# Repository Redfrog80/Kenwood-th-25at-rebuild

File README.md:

# Kenwood-th-25at-rebuild
Created a battery clam shell so I could replace the dead OEM battery of an old Kenwood handheld radio.
If you wish to replicate the battery using my models, all you need is a cheap usb-c 2S lipo charger, an appropriately sized 2S lipo, and a soldering iron.
If I ever return to this project, I will likely add screw holes so the battery can be dismantled, a physical switch to disconnect the battery from the charge controller (for storage), and a meter to display battery voltage.

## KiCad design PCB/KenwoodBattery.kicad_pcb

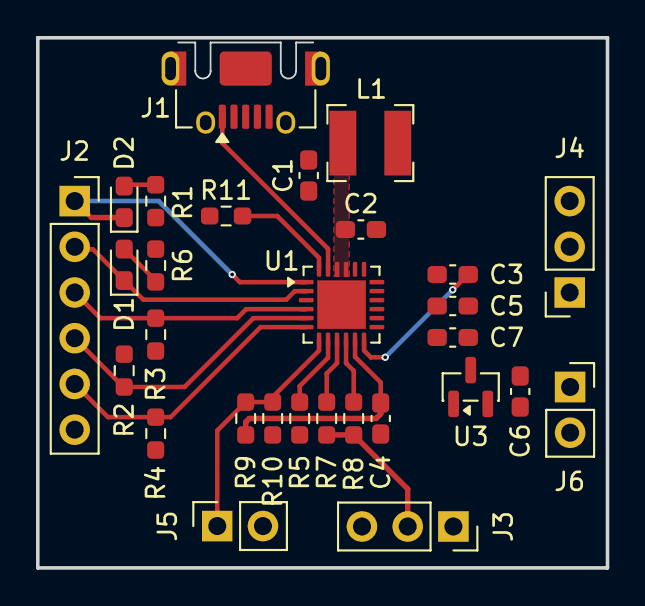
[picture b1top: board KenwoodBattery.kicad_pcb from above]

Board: 2 copper layers, 31.6 x 29.5 mm, 29 parts (0 on the bottom side), 23 nets.

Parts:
C1, C6: 1u; C_0603_1608Metric_Pad1.08x0.95mm_HandSolder
C2, C7: 10u; C_0603_1608Metric_Pad1.08x0.95mm_HandSolder
C3: 47n; C_0603_1608Metric_Pad1.08x0.95mm_HandSolder
C4: 4.7u; C_0603_1608Metric_Pad1.08x0.95mm_HandSolder
C5: 44u; C_0603_1608Metric_Pad1.08x0.95mm_HandSolder
D1, D2: LED_Small; LED_0603_1608Metric_Pad1.05x0.95mm_HandSolder
J1: USB_B_Micro; USB_Micro-AB_Molex_47590-0001
J2: Conn_01x06; PinSocket_1x06_P2.54mm_Vertical
J3, J4: Conn_01x03; PinSocket_1x03_P2.54mm_Vertical
J5, J6: Conn_01x02; PinSocket_1x02_P2.54mm_Vertical
L1: 1u; L_Bourns-SRN4018
R1, R6: 2.2k; R_0603_1608Metric_Pad0.98x0.95mm_HandSolder
R2, R3, R4, R5, R11: 10k; R_0603_1608Metric_Pad0.98x0.95mm_HandSolder
R7: 300; R_0603_1608Metric_Pad0.98x0.95mm_HandSolder
R8: 10; R_0603_1608Metric_Pad0.98x0.95mm_HandSolder
R9: 5.23k; R_0603_1608Metric_Pad0.98x0.95mm_HandSolder
R10: 30.1k; R_0603_1608Metric_Pad0.98x0.95mm_HandSolder
U1: BQ25887RGE; Texas_RGE0024H_VQFN-24-1EP_4x4mm_P0.5mm_EP2.7x2.7mm
U3: MAX6105; SOT-23

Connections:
BQ_INT: J2.5, R4.2, U1.6 (~INT)
BQ_PG: D2.1 (K), J2.1, U1.1 (~PG)
BQ_SCL: J2.4, R2.2, U1.5 (SCL)
BQ_SDA: J2.3, R3.1, U1.4 (SDA)
BQ_STAT: D1.1 (K), J2.2, U1.2 (STAT)
BQ_TS: J5.1, R9.2, R10.1, U1.7 (TS)
GND: C1.2, C2.2, C4.2, C5.2, C6.2, C7.2, J1.5 (GND), J2.6, J3.3, J4.3, J5.2, R5.2, R10.2, U1.19 (GND), U1.20 (GND), U1.25 (GND), U3.3 (GND)
unnamed: C2.1, L1.1, U1.21 (PMID), U1.22 (PMID)
unnamed: C3.1, L1.2, U1.17 (SW), U1.18 (SW)
unnamed: C5.1, U1.15 (SNS), U1.16 (SNS)
unnamed: D1.2 (A), R6.1
unnamed: D2.2 (A), R1.2
unnamed: J4.1, J4.2, J6.1
unnamed: C3.2, U1.12 (BTST)
unnamed: R8.1, U1.10 (CBSET)
unnamed: R5.1, U1.8 (ILIM)
unnamed: R7.2, U1.9 (MID)
unnamed: R11.2, U1.24 (PSEL)
unnamed: C4.1, R9.1, U1.11 (REGN)
VBAT: C7.1, J3.1, J6.2, U1.13 (BAT), U1.14 (BAT), U3.1 (IN)
VBATMID: J3.2, R7.1, R8.2
VUSB: C1.1, J1.1 (VBUS), U1.23 (VBUS)
V_REF: C6.1, R1.1, R2.1, R3.2, R4.1, R6.2, R11.1, U3.2 (OUT)

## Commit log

2026-03-15 Added project files
2026-04-06 Added project files for a potential charge controller for a fully custom battery.
